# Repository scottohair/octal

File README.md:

# octal
Octal - Programmers Calculator

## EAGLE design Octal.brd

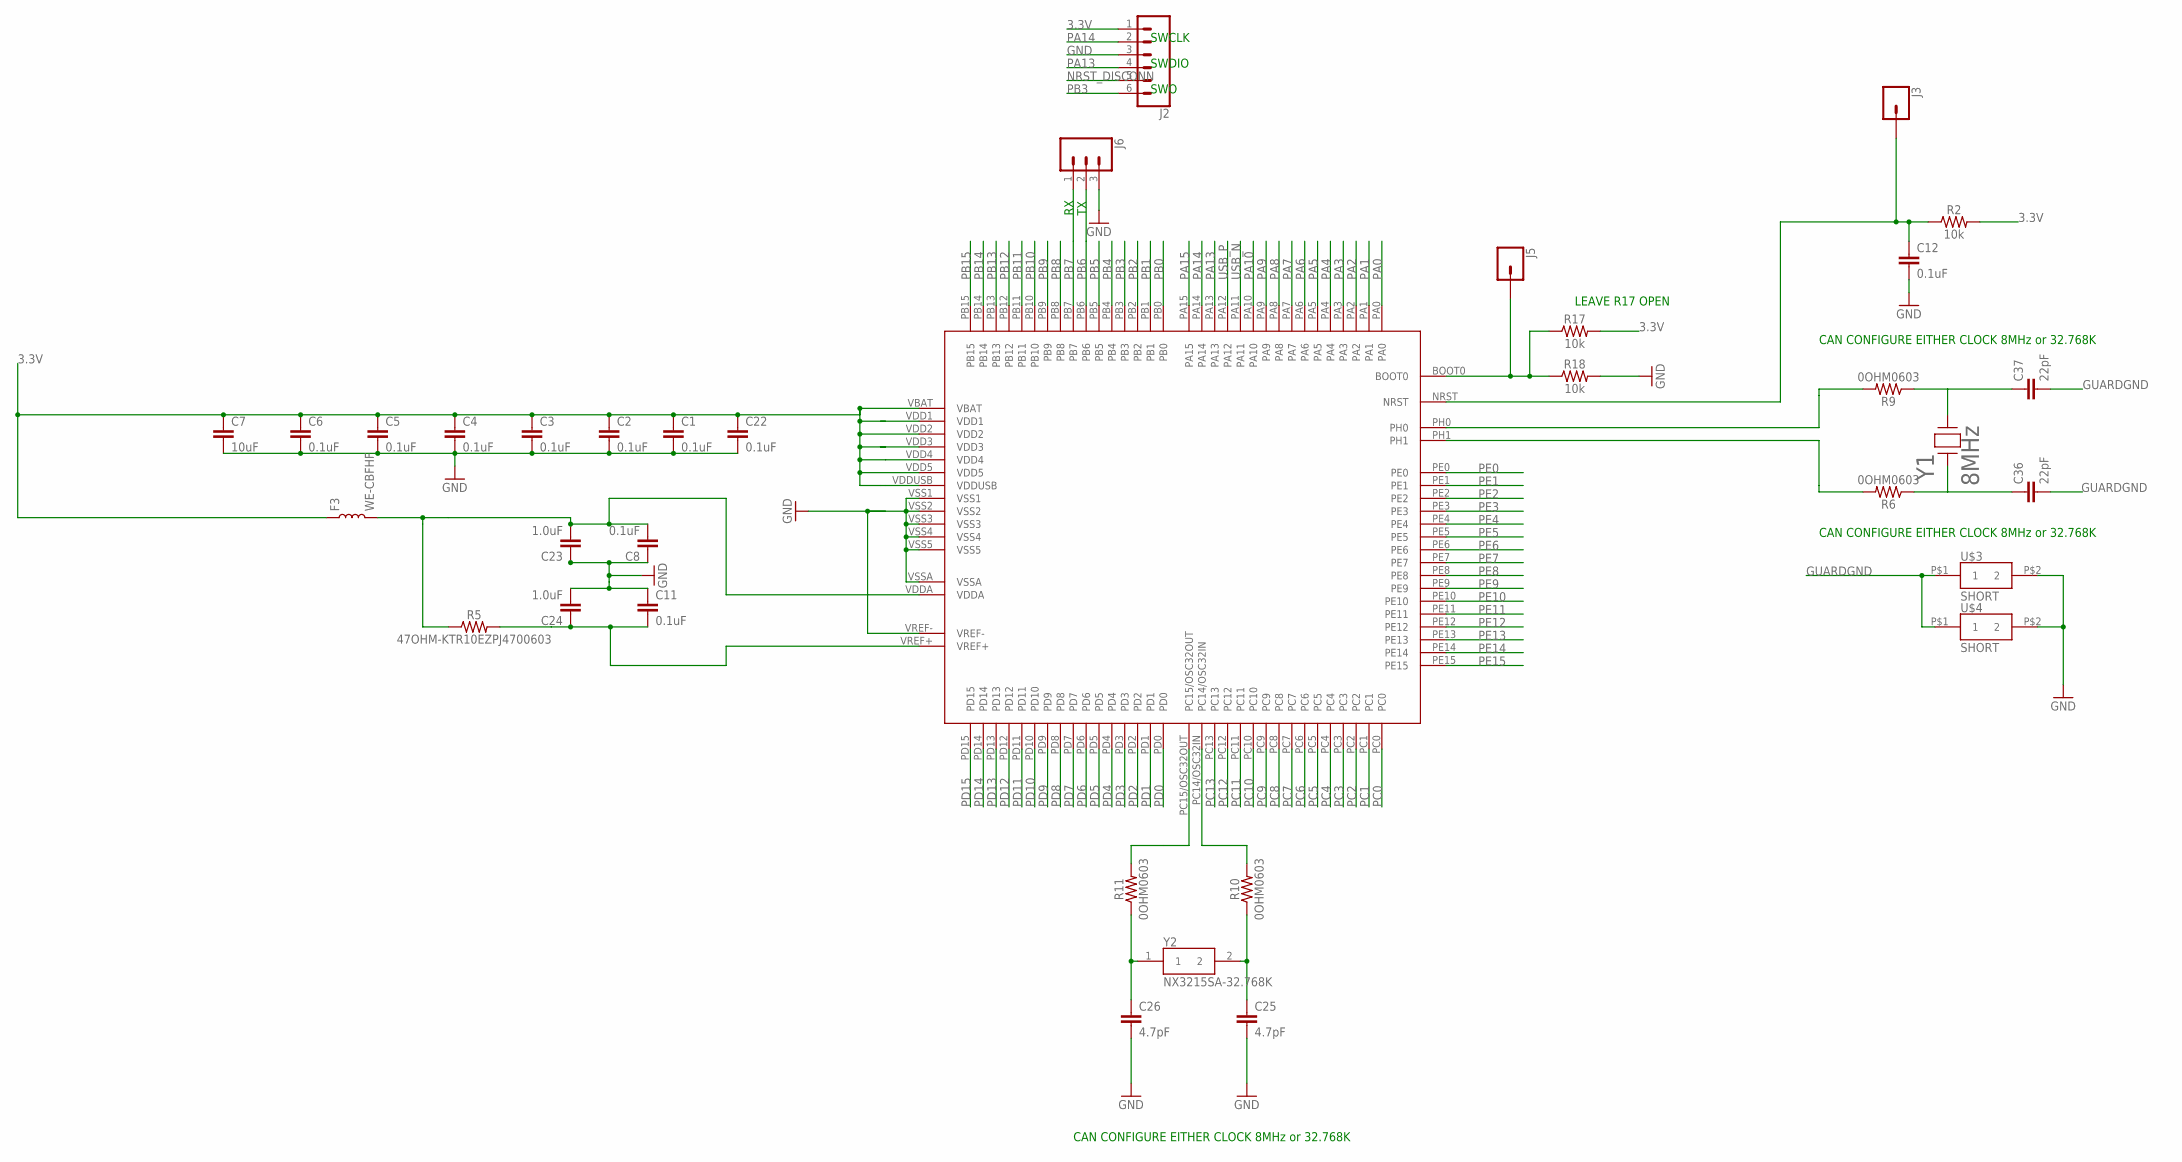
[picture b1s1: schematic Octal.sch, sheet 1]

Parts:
C1, C2, C3, C4, C5, C6, C8, C11, C12, C22: 0.1uF; 0603
C7: 10uF; 0603
C23, C24: 1.0uF; 0603
C25, C26: 4.7pF; 0603
C36, C37: 22pF; 0603
F3: WE-CBFHF; 0603
J2: CONN_06SILK_FEMALE_PTH; 1X06
J3, J5: CONN_01; 1X01
J6: CONN_03; 1X03
R2, R17, R18: 10k; 0603
R5: 47OHM-KTR10EZPJ4700603; 0603
R6, R9, R10, R11: 0OHM0603; 0603
U5: STM32L476VGT6; STM32L4_LQFP100
U$3, U$4: SHORT
Y1: 8MHz; CRYSTAL_HC49SDLF
Y2: NX3215SA-32.768K; NX3215SA32768KEXS00AMU00003

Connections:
3.3V: C1.1, C2.1, C3.1, C4.1, C5.1, C6.1, C7.1, C22.1, F3.1, J2.1, R2.2, R17.2, U5.VBAT, U5.VDD1, U5.VDD2, U5.VDD3, U5.VDD4, U5.VDD5, U5.VDDUSB; also elsewhere on the board
BOOT0: J5.1, R17.1, R18.1, U5.BOOT0
GND: C1.2, C2.2, C3.2, C4.2, C5.2, C6.2, C7.2, C8.1, C11.1, C12.2, C22.2, C23.1, C24.2, C25.2, C26.2, J2.3, J6.3, R18.2, U5.VREF-, U5.VSS1, U5.VSS2, U5.VSS3, U5.VSS4, U5.VSS5, U5.VSSA, U$3.P$2 (2), U$4.P$2 (2); also elsewhere on the board
GUARDGND: C36.2, C37.2, U$3.P$1 (1), U$4.P$1 (1)
unnamed: C8.2, C23.2, F3.2, R5.1, U5.VDDA
unnamed: C11.2, C24.1, R5.2, U5.VREF+
unnamed: R9.2, U5.PH0
unnamed: C37.1, R9.1, Y1.2
unnamed: C36.1, R6.1, Y1.1
unnamed: R6.2, U5.PH1
unnamed: C26.1, R11.1, Y2.1
unnamed: C25.1, R10.1, Y2.2
unnamed: R11.2, U5.PC15/OSC32OUT
unnamed: R10.2, U5.PC14/OSC32IN
NRST1: C12.1, J3.1, R2.1, U5.NRST
NRST_DISCONN: J2.5
PA0: U5.PA0; also elsewhere on the board
PA1: U5.PA1; also elsewhere on the board
PA2: U5.PA2; also elsewhere on the board
PA3: U5.PA3; also elsewhere on the board
PA4: U5.PA4; also elsewhere on the board
PA5: U5.PA5; also elsewhere on the board
PA6: U5.PA6; also elsewhere on the board
PA7: U5.PA7; also elsewhere on the board
PA8: U5.PA8; also elsewhere on the board
PA9: U5.PA9; also elsewhere on the board
PA10: U5.PA10; also elsewhere on the board
PA13: J2.4, U5.PA13
PA14: J2.2, U5.PA14
PA15: U5.PA15; also elsewhere on the board
PB0: U5.PB0; also elsewhere on the board
PB1: U5.PB1; also elsewhere on the board
PB2: U5.PB2; also elsewhere on the board
PB3: J2.6, U5.PB3
PB4: U5.PB4; also elsewhere on the board
PB5: U5.PB5
PB6: J6.2, U5.PB6
PB7: J6.1, U5.PB7
PB8: U5.PB8
PB9: U5.PB9
PB10: U5.PB10; also elsewhere on the board
PB11: U5.PB11; also elsewhere on the board
PB12: U5.PB12; also elsewhere on the board
PB13: U5.PB13; also elsewhere on the board
PB14: U5.PB14; also elsewhere on the board
PB15: U5.PB15; also elsewhere on the board
PC0: U5.PC0; also elsewhere on the board
PC1: U5.PC1; also elsewhere on the board
PC2: U5.PC2; also elsewhere on the board
PC3: U5.PC3; also elsewhere on the board
PC4: U5.PC4; also elsewhere on the board
PC5: U5.PC5; also elsewhere on the board
PC6: U5.PC6; also elsewhere on the board
PC7: U5.PC7; also elsewhere on the board
PC8: U5.PC8; also elsewhere on the board
PC9: U5.PC9; also elsewhere on the board
PC10: U5.PC10; also elsewhere on the board
PC11: U5.PC11; also elsewhere on the board
PC12: U5.PC12; also elsewhere on the board
PC13: U5.PC13
PD0: U5.PD0; also elsewhere on the board
PD1: U5.PD1; also elsewhere on the board
PD2: U5.PD2; also elsewhere on the board
PD3: U5.PD3; also elsewhere on the board
PD4: U5.PD4; also elsewhere on the board
PD5: U5.PD5; also elsewhere on the board
PD6: U5.PD6; also elsewhere on the board
PD7: U5.PD7; also elsewhere on the board
PD8: U5.PD8; also elsewhere on the board
PD9: U5.PD9; also elsewhere on the board
PD10: U5.PD10; also elsewhere on the board
PD11: U5.PD11; also elsewhere on the board
PD12: U5.PD12; also elsewhere on the board
PD13: U5.PD13; also elsewhere on the board
PD14: U5.PD14; also elsewhere on the board
PD15: U5.PD15; also elsewhere on the board
PE0: U5.PE0; also elsewhere on the board
PE1: U5.PE1; also elsewhere on the board
PE2: U5.PE2; also elsewhere on the board
PE3: U5.PE3; also elsewhere on the board
PE4: U5.PE4; also elsewhere on the board
PE5: U5.PE5; also elsewhere on the board
PE6: U5.PE6; also elsewhere on the board
PE7: U5.PE7; also elsewhere on the board
PE8: U5.PE8; also elsewhere on the board
PE9: U5.PE9; also elsewhere on the board
PE10: U5.PE10; also elsewhere on the board
PE11: U5.PE11; also elsewhere on the board
PE12: U5.PE12; also elsewhere on the board
PE13: U5.PE13; also elsewhere on the board
PE14: U5.PE14; also elsewhere on the board
PE15: U5.PE15; also elsewhere on the board
USB_N: U5.PA11; also elsewhere on the board
USB_P: U5.PA12; also elsewhere on the board

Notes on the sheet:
SWO
SWCLK
SWDIO
CAN CONFIGURE EITHER CLOCK 8MHz or 32.768K
LEAVE R17 OPEN

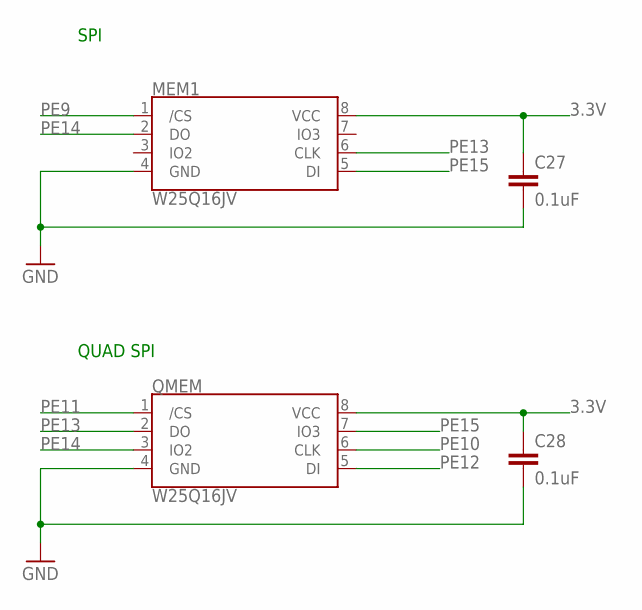
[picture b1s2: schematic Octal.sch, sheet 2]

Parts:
C27, C28: 0.1uF; 0603
MEM1: W25Q16JV; SOIC-8
QMEM: W25Q16JV; SOIC-8

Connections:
3.3V: C27.1, C28.1, MEM1.8 (VCC), QMEM.8 (VCC); also elsewhere on the board
GND: C27.2, C28.2, MEM1.4 (GND), QMEM.4 (GND); also elsewhere on the board
PE9: MEM1.1 (/CS); also elsewhere on the board
PE10: QMEM.6 (CLK); also elsewhere on the board
PE11: QMEM.1 (/CS); also elsewhere on the board
PE12: QMEM.5 (DI); also elsewhere on the board
PE13: MEM1.6 (CLK), QMEM.2 (DO); also elsewhere on the board
PE14: MEM1.2 (DO), QMEM.3 (IO2); also elsewhere on the board
PE15: MEM1.5 (DI), QMEM.7 (IO3); also elsewhere on the board

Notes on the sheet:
QUAD SPI
SPI

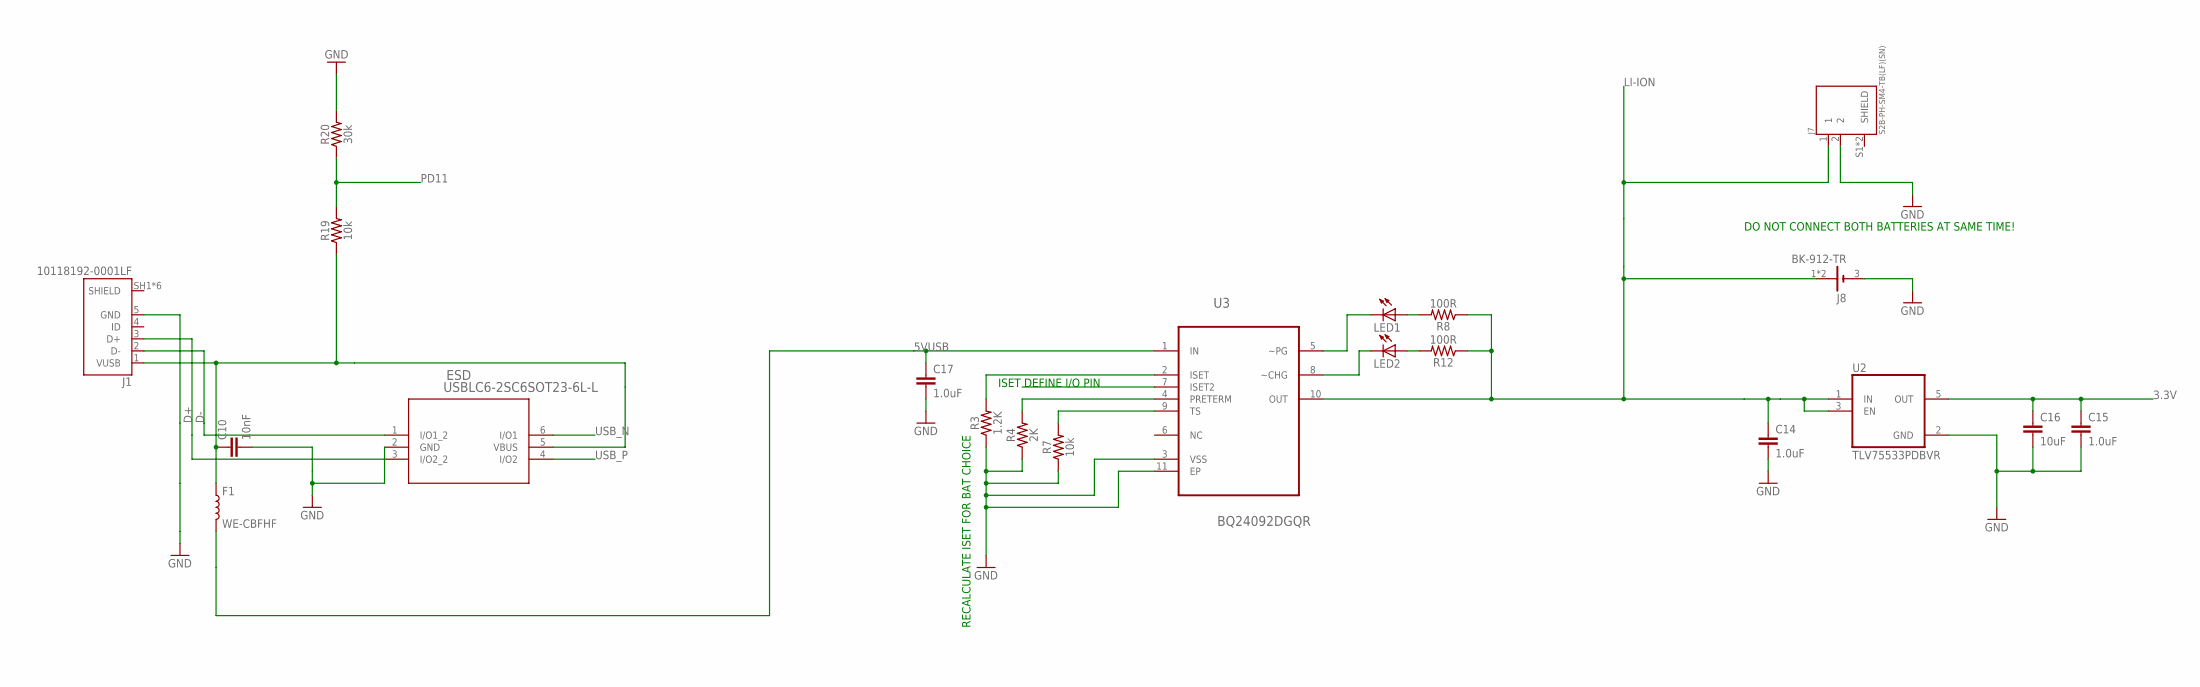
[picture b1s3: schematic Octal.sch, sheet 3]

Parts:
C10: 10nF; 0603
C14, C15, C17: 1.0uF; SPARKFUN-CAPACITORS_0603
C16: 10uF; 0603
ESD: USBLC6-2SC6SOT23-6L-L; SOT23-6L-L
F1: WE-CBFHF; 0603
J1: 10118192-0001LF; AMPHENOL_10118192-0001LF
J7: S2B-PH-SM4-TB(LF)(SN); JST_S2B-PH-SM4-TB(LF)(SN)
J8: BK-912-TR; MPD_BK-912-TR
LED1, LED2: LEDCHIP-LED0603; CHIP-LED0603
R3: 1.2K; SPARKFUN-RESISTORS_0603:1
R4: 2K; SPARKFUN-RESISTORS_0603:1
R7, R19: 10k; SPARKFUN-RESISTORS_0603:1
R8, R12: 100R; SPARKFUN-RESISTORS_0603:1
R20: 30k; SPARKFUN-RESISTORS_0603:1
U2: TLV75533PDBVR; SOT95P280X145-5N
U3: BQ24092DGQR; SOP50P490X110-11N

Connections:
3.3V: C15.1, C16.1, U2.5 (OUT); also elsewhere on the board
5VUSB: C17.1, F1.2, U3.1 (IN)
D+: ESD.3 (I/O2_2), J1.3 (D+)
D-: ESD.1 (I/O1_2), J1.2 (D-)
GND: C10.2, C14.2, C15.2, C16.2, C17.2, ESD.2 (GND), J1.5 (GND), J7.2, J8.3 (-), R3.1, R4.1, R7.1, R20.2, U2.2 (GND), U3.3 (VSS), U3.11 (EP); also elsewhere on the board
LI-ION: C14.1, J7.1, J8.1 (+), J8.2 (+), R8.1, R12.1, U2.1 (IN), U2.3 (EN), U3.10 (OUT)
unnamed: R3.2, U3.2 (ISET)
unnamed: R7.2, U3.9 (TS)
unnamed: R4.2, U3.4 (PRETERM)
unnamed: LED1.C, U3.5 (~PG)
unnamed: LED2.C, U3.8 (~CHG)
unnamed: LED1.A, R8.2
unnamed: LED2.A, R12.2
PD11: R19.2, R20.1; also elsewhere on the board
USB_N: ESD.6 (I/O1); also elsewhere on the board
USB_P: ESD.4 (I/O2); also elsewhere on the board
VBUS: C10.1, ESD.5 (VBUS), F1.1, J1.1 (VUSB), R19.1

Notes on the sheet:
ISET DEFINE I/O PIN
RECALCULATE ISET FOR BAT CHOICE
DO NOT CONNECT BOTH BATTERIES AT SAME TIME!

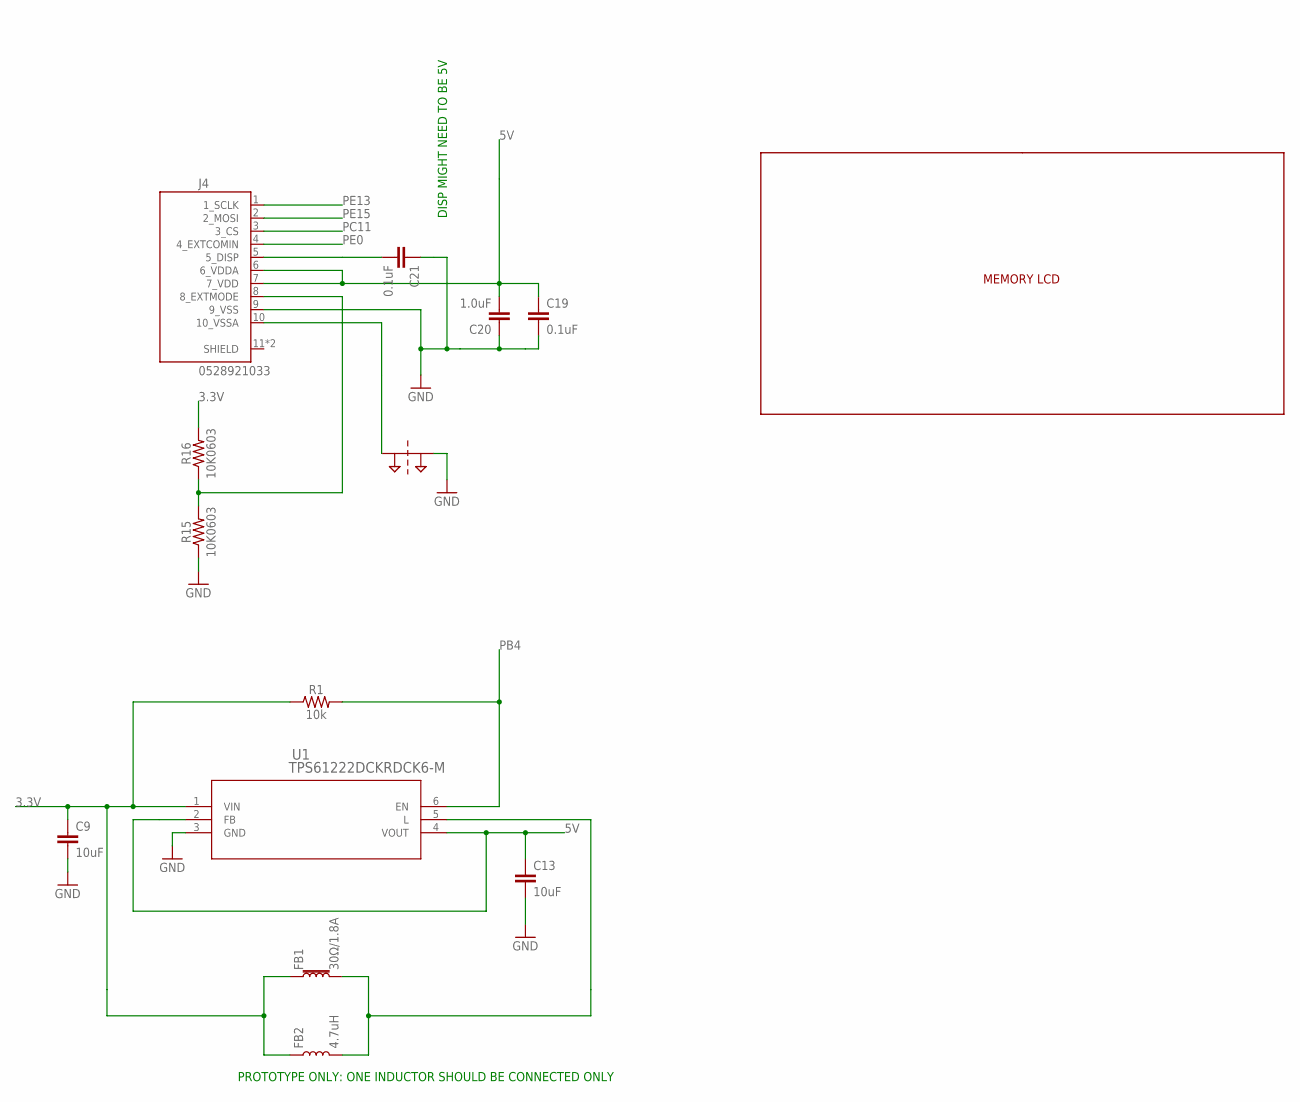
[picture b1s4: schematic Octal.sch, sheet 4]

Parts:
C9, C13: 10uF; 0603
C19, C21: 0.1uF; 0603
C20: 1.0uF; 0603
FB1: 30Ω/1.8A; 0603
FB2: 4.7uH; CIG22H4R7MNE
J4: 0528921033; MOLEX_0528921033
R1: 10k; SPARKFUN-RESISTORS_0603:1
R15, R16: 10K0603; 0603
SUPPLY1: 2PT_GND_TIE
U1: TPS61222DCKRDCK6-M; DCK6-M
U$2: LS027B7DH01

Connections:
3.3V: C9.1, FB1.1, FB2.1, R1.1, R16.2, U1.1 (VIN); also elsewhere on the board
5V: C13.1, C19.1, C20.2, J4.6 (6_VDDA), J4.7 (7_VDD), U1.2 (FB), U1.4 (VOUT)
ARTN: J4.10 (10_VSSA), SUPPLY1.P$1
GND: C9.2, C13.2, C19.2, C20.1, C21.1, J4.9 (9_VSS), R15.1, SUPPLY1.P$2, U1.3 (GND); also elsewhere on the board
unnamed: FB1.2, FB2.2, U1.5 (L)
unnamed: C21.2, J4.5 (5_DISP)
unnamed: J4.8 (8_EXTMODE), R15.2, R16.1
PB4: R1.2, U1.6 (EN); also elsewhere on the board
PC11: J4.3 (3_CS); also elsewhere on the board
PE0: J4.4 (4_EXTCOMIN); also elsewhere on the board
PE13: J4.1 (1_SCLK); also elsewhere on the board
PE15: J4.2 (2_MOSI); also elsewhere on the board

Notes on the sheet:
PROTOTYPE ONLY: ONE INDUCTOR SHOULD BE CONNECTED ONLY
DISP MIGHT NEED TO BE 5V

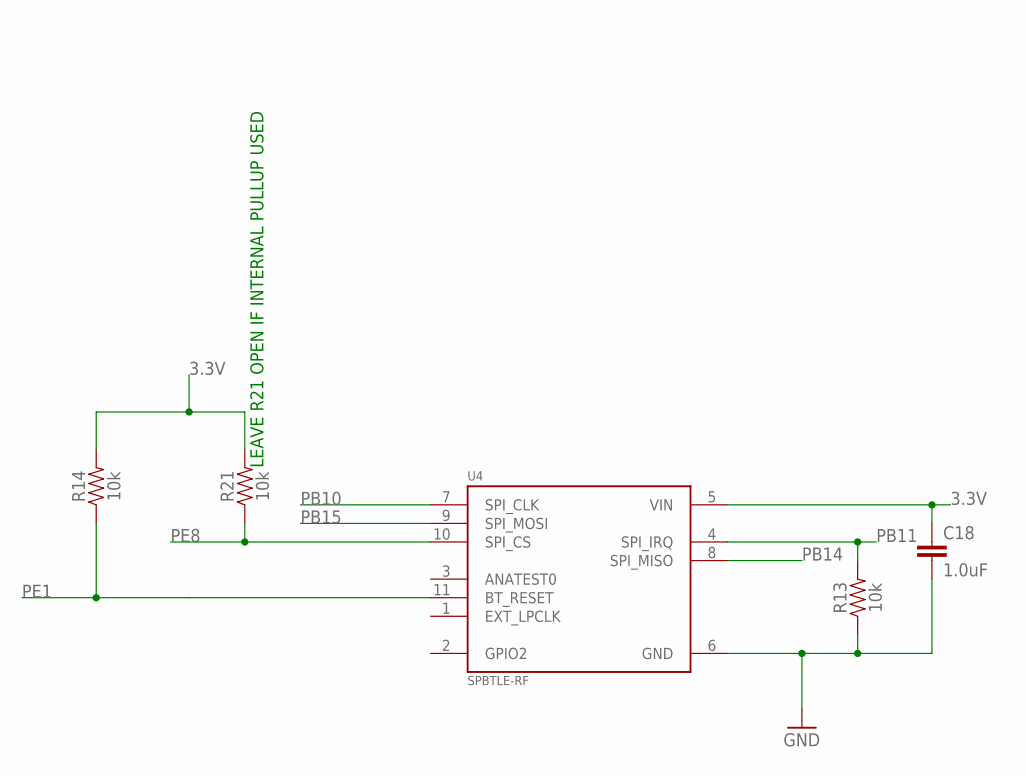
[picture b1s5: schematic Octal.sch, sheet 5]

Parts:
C18: 1.0uF; SPARKFUN-CAPACITORS_0603
R13, R14, R21: 10k; SPARKFUN-RESISTORS_0603:1
U4: SPBTLE-RF; XCVR_SPBTLE-RF

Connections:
3.3V: C18.1, R14.2, R21.2, U4.5 (VIN); also elsewhere on the board
GND: C18.2, R13.1, U4.6 (GND); also elsewhere on the board
PB10: U4.7 (SPI_CLK); also elsewhere on the board
PB11: R13.2, U4.4 (SPI_IRQ); also elsewhere on the board
PB14: U4.8 (SPI_MISO); also elsewhere on the board
PB15: U4.9 (SPI_MOSI); also elsewhere on the board
PE1: R14.1, U4.11 (BT_RESET); also elsewhere on the board
PE8: R21.1, U4.10 (SPI_CS); also elsewhere on the board

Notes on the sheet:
LEAVE R21 OPEN IF INTERNAL PULLUP USED

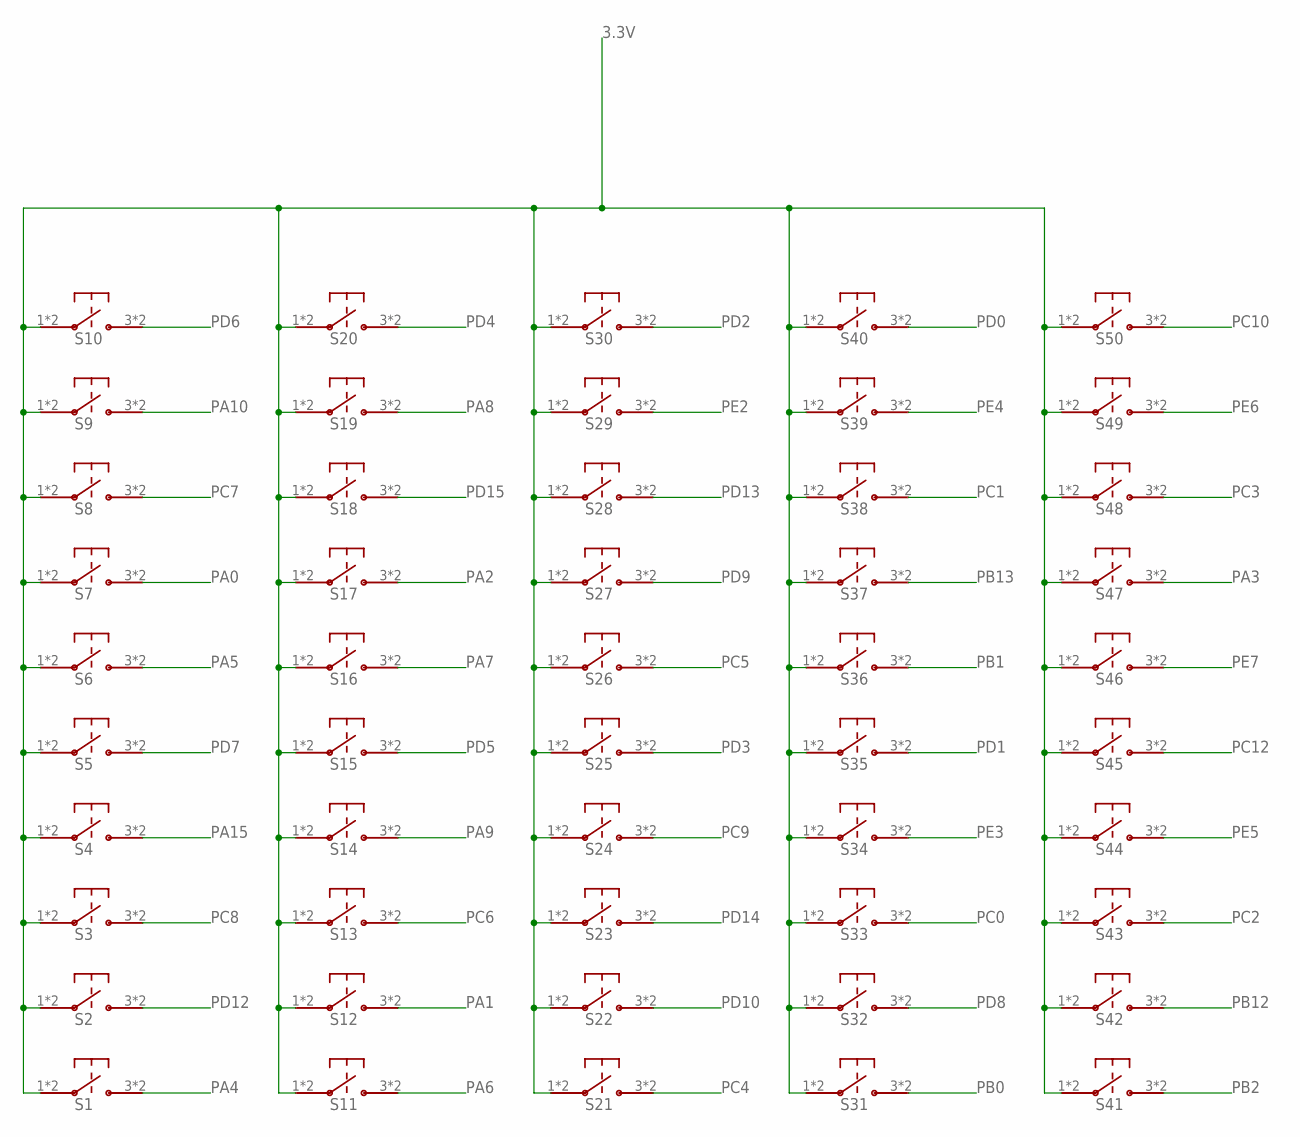
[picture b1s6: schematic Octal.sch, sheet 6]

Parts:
S1, S2, S3, S4, S5, S6, S7, S8, S9, S10, S11, S12, S13, S14, S15, S16, S17, S18, S19, S20, S21, S22, S23, S24, S25, S26, S27, S28, S29, S30, S31, S32, S33, S34, S35, S36, S37, S38, S39, S40, S41, S42, S43, S44, S45, S46, S47, S48, S49, S50: TL3315NF100Q

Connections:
3.3V: S1.1, S1.2, S2.1, S2.2, S3.1, S3.2, S4.1, S4.2, S5.1, S5.2, S6.1, S6.2, S7.1, S7.2, S8.1, S8.2, S9.1, S9.2, S10.1, S10.2, S11.1, S11.2, S12.1, S12.2, S13.1, S13.2, S14.1, S14.2, S15.1, S15.2, S16.1, S16.2, S17.1, S17.2, S18.1, S18.2, S19.1, S19.2, S20.1, S20.2, S21.1, S21.2, S22.1, S22.2, S23.1, S23.2, S24.1, S24.2, S25.1, S25.2, S26.1, S26.2, S27.1, S27.2, S28.1, S28.2, S29.1, S29.2, S30.1, S30.2, S31.1, S31.2, S32.1, S32.2, S33.1, S33.2, S34.1, S34.2, S35.1, S35.2, S36.1, S36.2, S37.1, S37.2, S38.1, S38.2, S39.1, S39.2, S40.1, S40.2, S41.1, S41.2, S42.1, S42.2, S43.1, S43.2, S44.1, S44.2, S45.1, S45.2, S46.1, S46.2, S47.1, S47.2, S48.1, S48.2, S49.1, S49.2, S50.1, S50.2; also elsewhere on the board
PA0: S7.3, S7.4; also elsewhere on the board
PA1: S12.3, S12.4; also elsewhere on the board
PA2: S17.3, S17.4; also elsewhere on the board
PA3: S47.3, S47.4; also elsewhere on the board
PA4: S1.3, S1.4; also elsewhere on the board
PA5: S6.3, S6.4; also elsewhere on the board
PA6: S11.3, S11.4; also elsewhere on the board
PA7: S16.3, S16.4; also elsewhere on the board
PA8: S19.3, S19.4; also elsewhere on the board
PA9: S14.3, S14.4; also elsewhere on the board
PA10: S9.3, S9.4; also elsewhere on the board
PA15: S4.3, S4.4; also elsewhere on the board
PB0: S31.3, S31.4; also elsewhere on the board
PB1: S36.3, S36.4; also elsewhere on the board
PB2: S41.3, S41.4; also elsewhere on the board
PB12: S42.3, S42.4; also elsewhere on the board
PB13: S37.3, S37.4; also elsewhere on the board
PC0: S33.3, S33.4; also elsewhere on the board
PC1: S38.3, S38.4; also elsewhere on the board
PC2: S43.3, S43.4; also elsewhere on the board
PC3: S48.3, S48.4; also elsewhere on the board
PC4: S21.3, S21.4; also elsewhere on the board
PC5: S26.3, S26.4; also elsewhere on the board
PC6: S13.3, S13.4; also elsewhere on the board
PC7: S8.3, S8.4; also elsewhere on the board
PC8: S3.3, S3.4; also elsewhere on the board
PC9: S24.3, S24.4; also elsewhere on the board
PC10: S50.3, S50.4; also elsewhere on the board
PC12: S45.3, S45.4; also elsewhere on the board
PD0: S40.3, S40.4; also elsewhere on the board
PD1: S35.3, S35.4; also elsewhere on the board
PD2: S30.3, S30.4; also elsewhere on the board
PD3: S25.3, S25.4; also elsewhere on the board
PD4: S20.3, S20.4; also elsewhere on the board
PD5: S15.3, S15.4; also elsewhere on the board
PD6: S10.3, S10.4; also elsewhere on the board
PD7: S5.3, S5.4; also elsewhere on the board
PD8: S32.3, S32.4; also elsewhere on the board
PD9: S27.3, S27.4; also elsewhere on the board
PD10: S22.3, S22.4; also elsewhere on the board
PD12: S2.3, S2.4; also elsewhere on the board
PD13: S28.3, S28.4; also elsewhere on the board
PD14: S23.3, S23.4; also elsewhere on the board
PD15: S18.3, S18.4; also elsewhere on the board
PE2: S29.3, S29.4; also elsewhere on the board
PE3: S34.3, S34.4; also elsewhere on the board
PE4: S39.3, S39.4; also elsewhere on the board
PE5: S44.3, S44.4; also elsewhere on the board
PE6: S49.3, S49.4; also elsewhere on the board
PE7: S46.3, S46.4; also elsewhere on the board

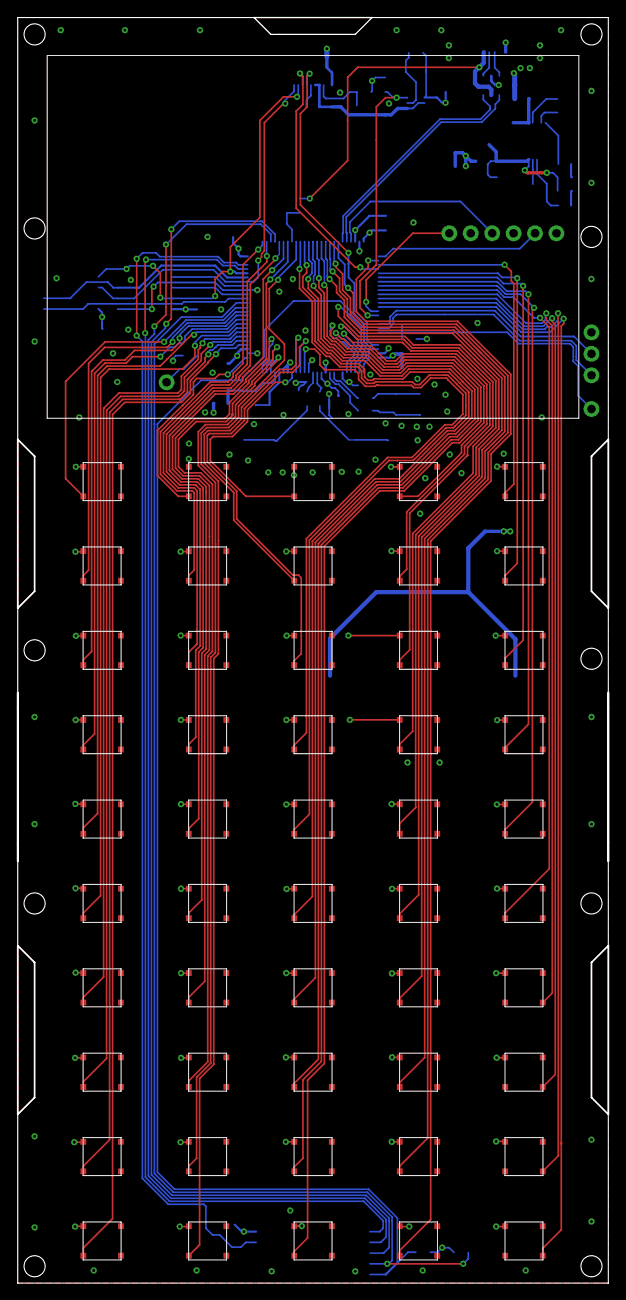
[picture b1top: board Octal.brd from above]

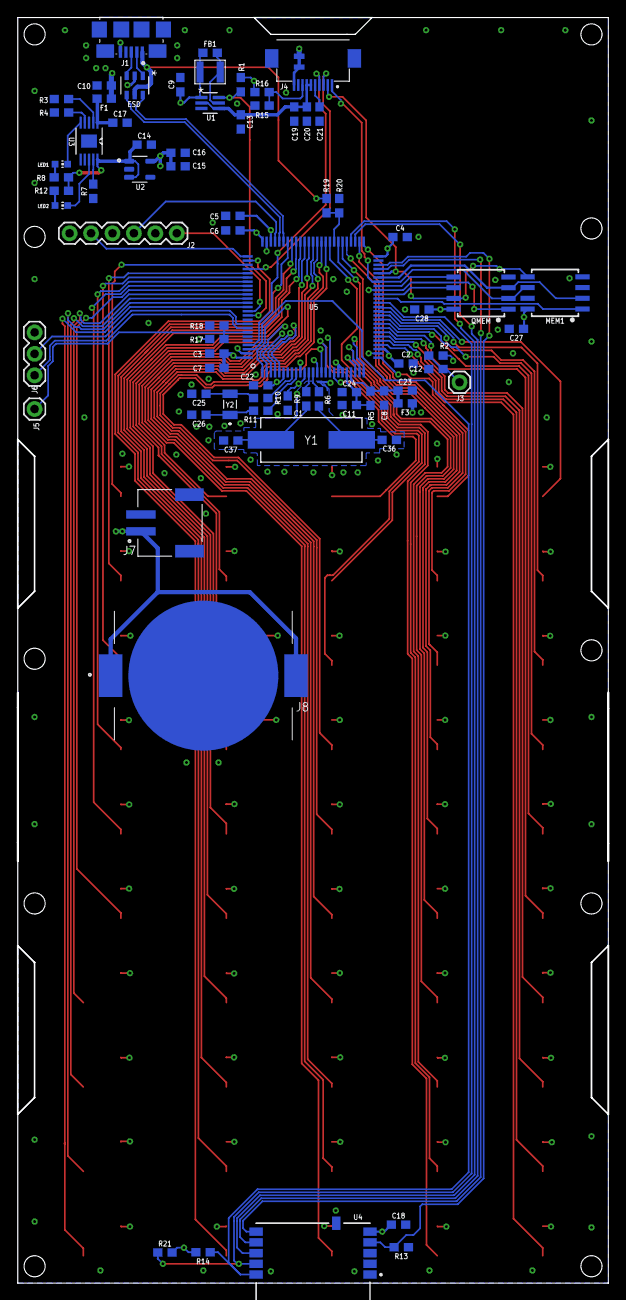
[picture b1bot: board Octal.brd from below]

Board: 4 copper layers, 70.0 x 150.0 mm, 129 parts (78 on the bottom side), 106 nets.

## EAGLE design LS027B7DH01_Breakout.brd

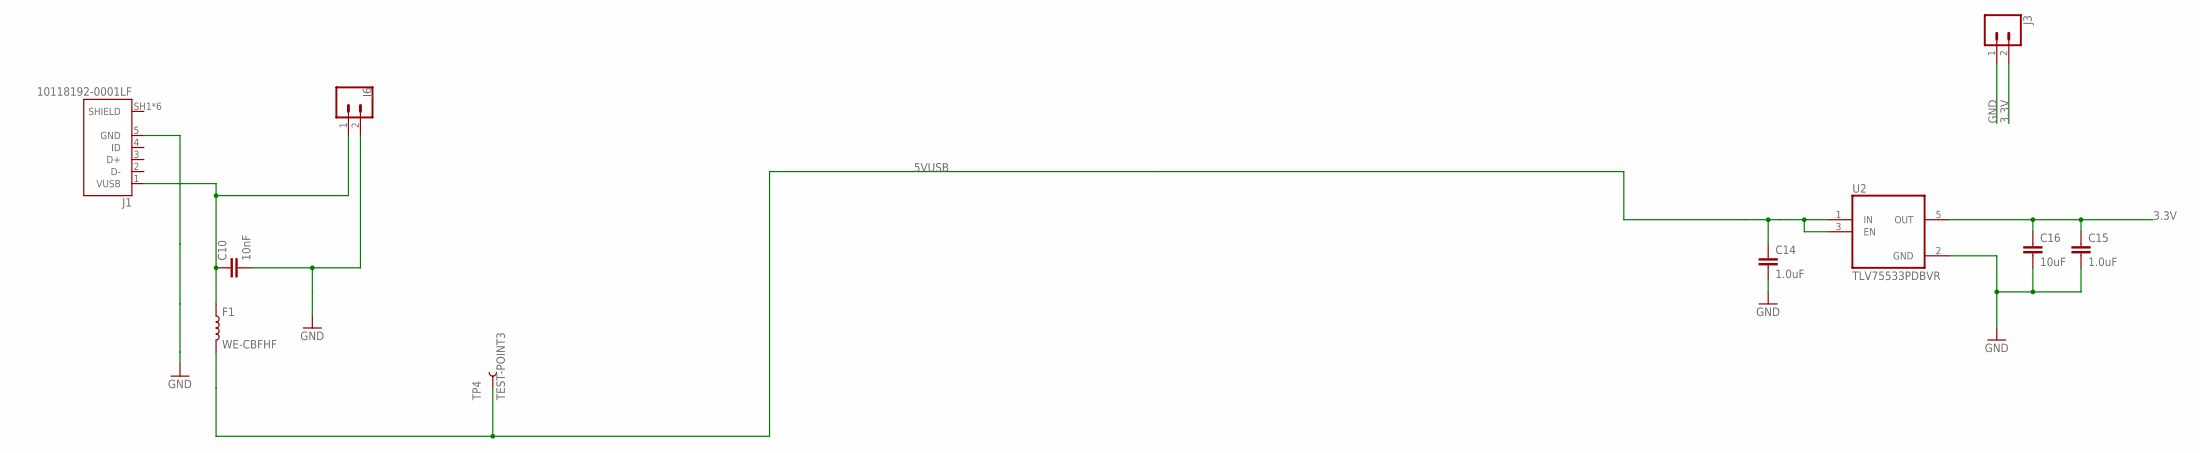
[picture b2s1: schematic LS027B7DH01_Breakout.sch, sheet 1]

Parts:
C10: 10nF; 0603
C14, C15: 1.0uF; SPARKFUN-CAPACITORS_0603
C16: 10uF; 0603
F1: WE-CBFHF; 0603
J1: 10118192-0001LF; AMPHENOL_10118192-0001LF
J3, J6: CONN_02; 1X02
TP4: TEST-POINT3; PAD.03X.03
U2: TLV75533PDBVR; SOT95P280X145-5N

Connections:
3.3V: C15.1, C16.1, J3.2, U2.5 (OUT); also elsewhere on the board
5VUSB: C14.1, F1.2, TP4.P$1, U2.1 (IN), U2.3 (EN)
GND: C10.2, C14.2, C15.2, C16.2, J1.5 (GND), J3.1, J6.2, U2.2 (GND); also elsewhere on the board
VBUS: C10.1, F1.1, J1.1 (VUSB), J6.1

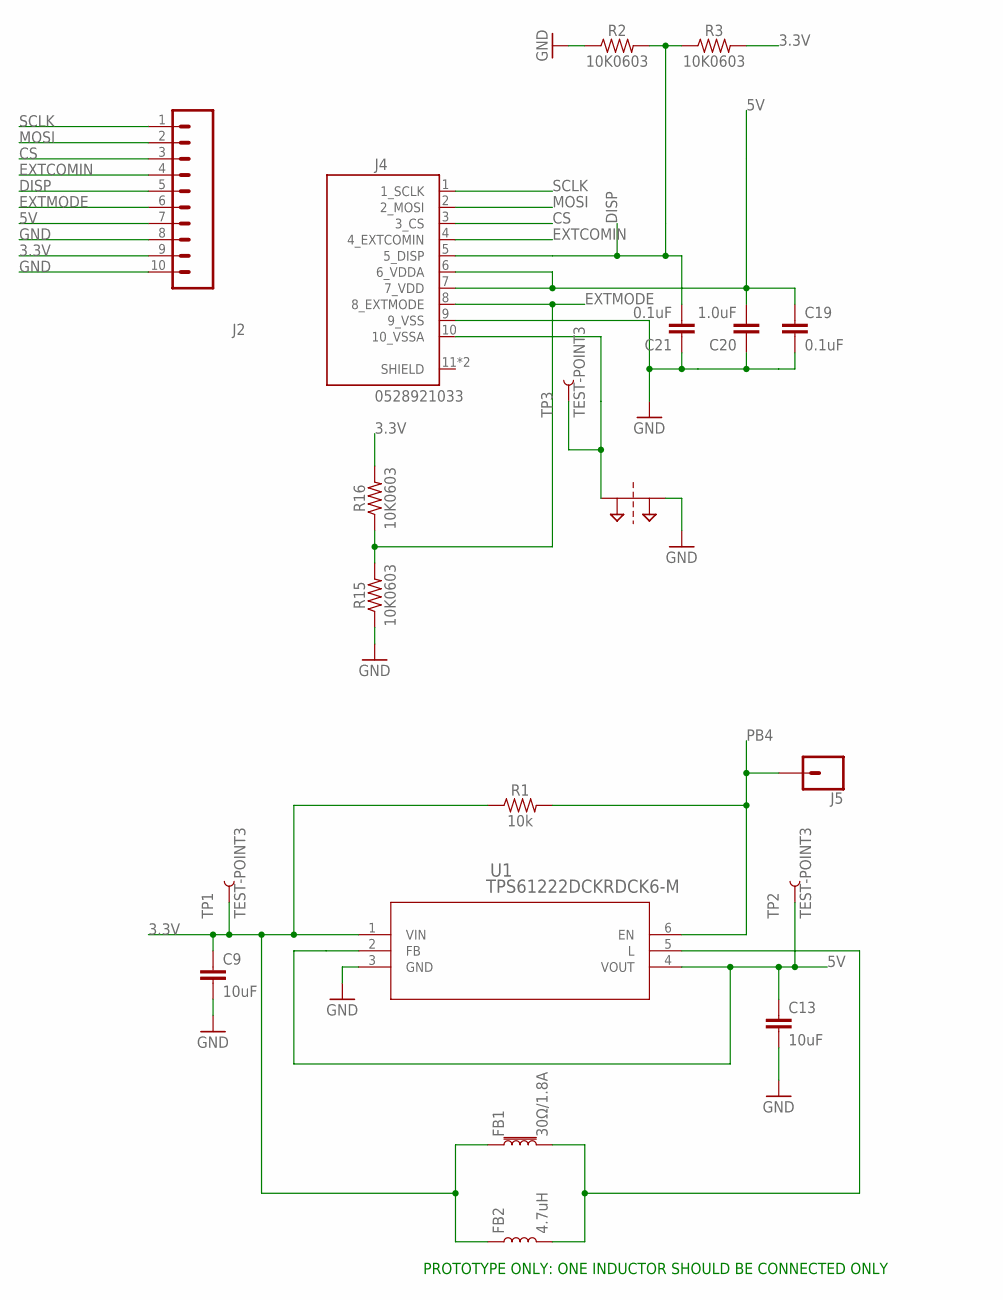
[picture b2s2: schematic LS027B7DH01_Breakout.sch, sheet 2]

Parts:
C9, C13: 10uF; 0603
C19, C21: 0.1uF; 0603
C20: 1.0uF; 0603
FB1: 30Ω/1.8A; 0603
FB2: 4.7uH; CIG22H4R7MNE
J2: CONN_10"; 1X10
J4: 0528921033; MOLEX_0528921033
J5: CONN_01; 1X01
R1: 10k; SPARKFUN-RESISTORS_0603:1
R2, R3, R15, R16: 10K0603; 0603
SUPPLY1: 2PT_GND_TIE
TP1, TP2, TP3: TEST-POINT3; PAD.03X.03
U1: TPS61222DCKRDCK6-M; DCK6-M

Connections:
3.3V: C9.1, FB1.1, FB2.1, J2.9, R1.1, R3.2, R16.2, TP1.P$1, U1.1 (VIN); also elsewhere on the board
5V: C13.1, C19.1, C20.2, J2.7, J4.6 (6_VDDA), J4.7 (7_VDD), TP2.P$1, U1.2 (FB), U1.4 (VOUT)
ARTN: J4.10 (10_VSSA), SUPPLY1.P$1, TP3.P$1
CS: J2.3, J4.3 (3_CS)
DISP: C21.2, J2.5, J4.5 (5_DISP), R2.2, R3.1
EXTCOMIN: J2.4, J4.4 (4_EXTCOMIN)
EXTMODE: J2.6, J4.8 (8_EXTMODE), R15.2, R16.1
GND: C9.2, C13.2, C19.2, C20.1, C21.1, J2.8, J2.10, J4.9 (9_VSS), R2.1, R15.1, SUPPLY1.P$2, U1.3 (GND); also elsewhere on the board
MOSI: J2.2, J4.2 (2_MOSI)
unnamed: FB1.2, FB2.2, U1.5 (L)
PB4: J5.1, R1.2, U1.6 (EN)
SCLK: J2.1, J4.1 (1_SCLK)

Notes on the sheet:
PROTOTYPE ONLY: ONE INDUCTOR SHOULD BE CONNECTED ONLY

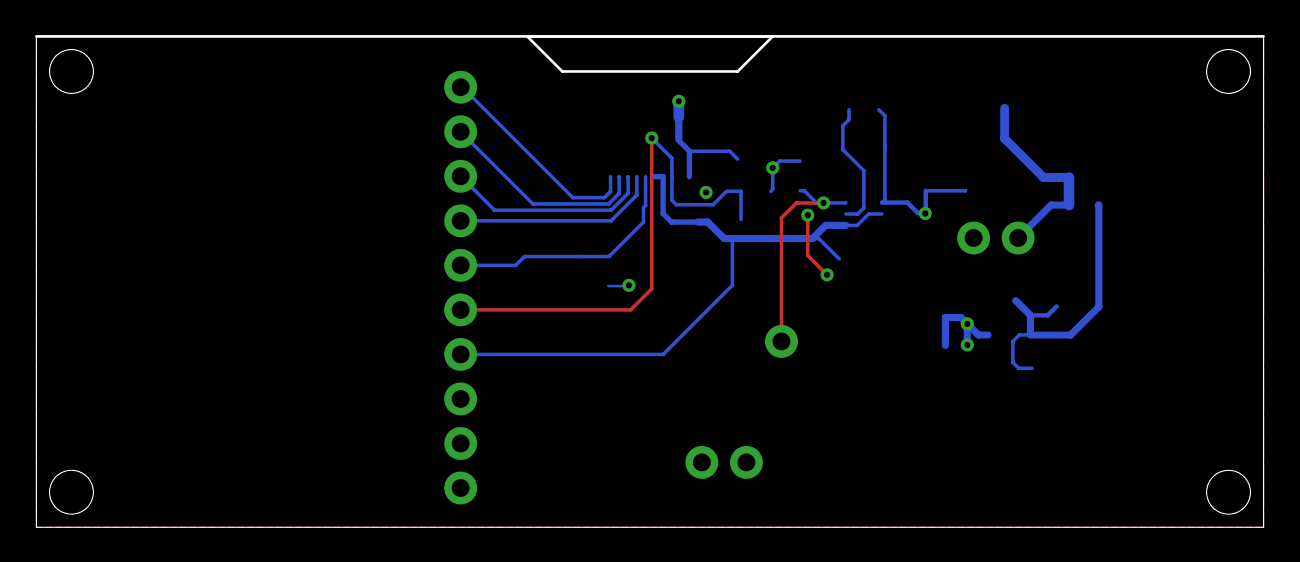
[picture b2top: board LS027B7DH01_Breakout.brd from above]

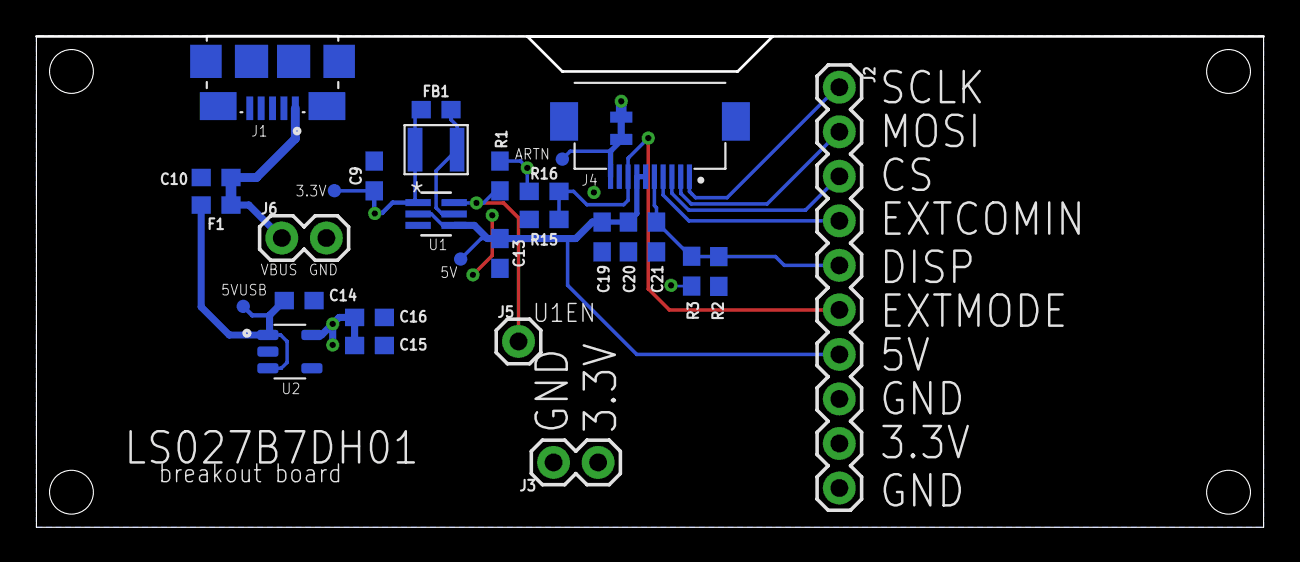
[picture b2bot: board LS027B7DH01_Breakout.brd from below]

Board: 2 copper layers, 70.0 x 28.0 mm, 30 parts (30 on the bottom side), 14 nets.

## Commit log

2021-08-26 Add files via upload
    Added Octal STM32L4 calculator design, LS027B7DH01 breakout board and BOM for Octal project
2021-08-26 Add files via upload
    Adding PDF of schematic
2021-08-27 Add files via upload
    Adding Octal source, requires Mbed OS to be installed in root

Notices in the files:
parts and their libraries:
SparkFun-Capacitors: Licensing: Creative Commons ShareAlike 4.0 International - https://creativecommons.org/licenses/by-sa/4.0
